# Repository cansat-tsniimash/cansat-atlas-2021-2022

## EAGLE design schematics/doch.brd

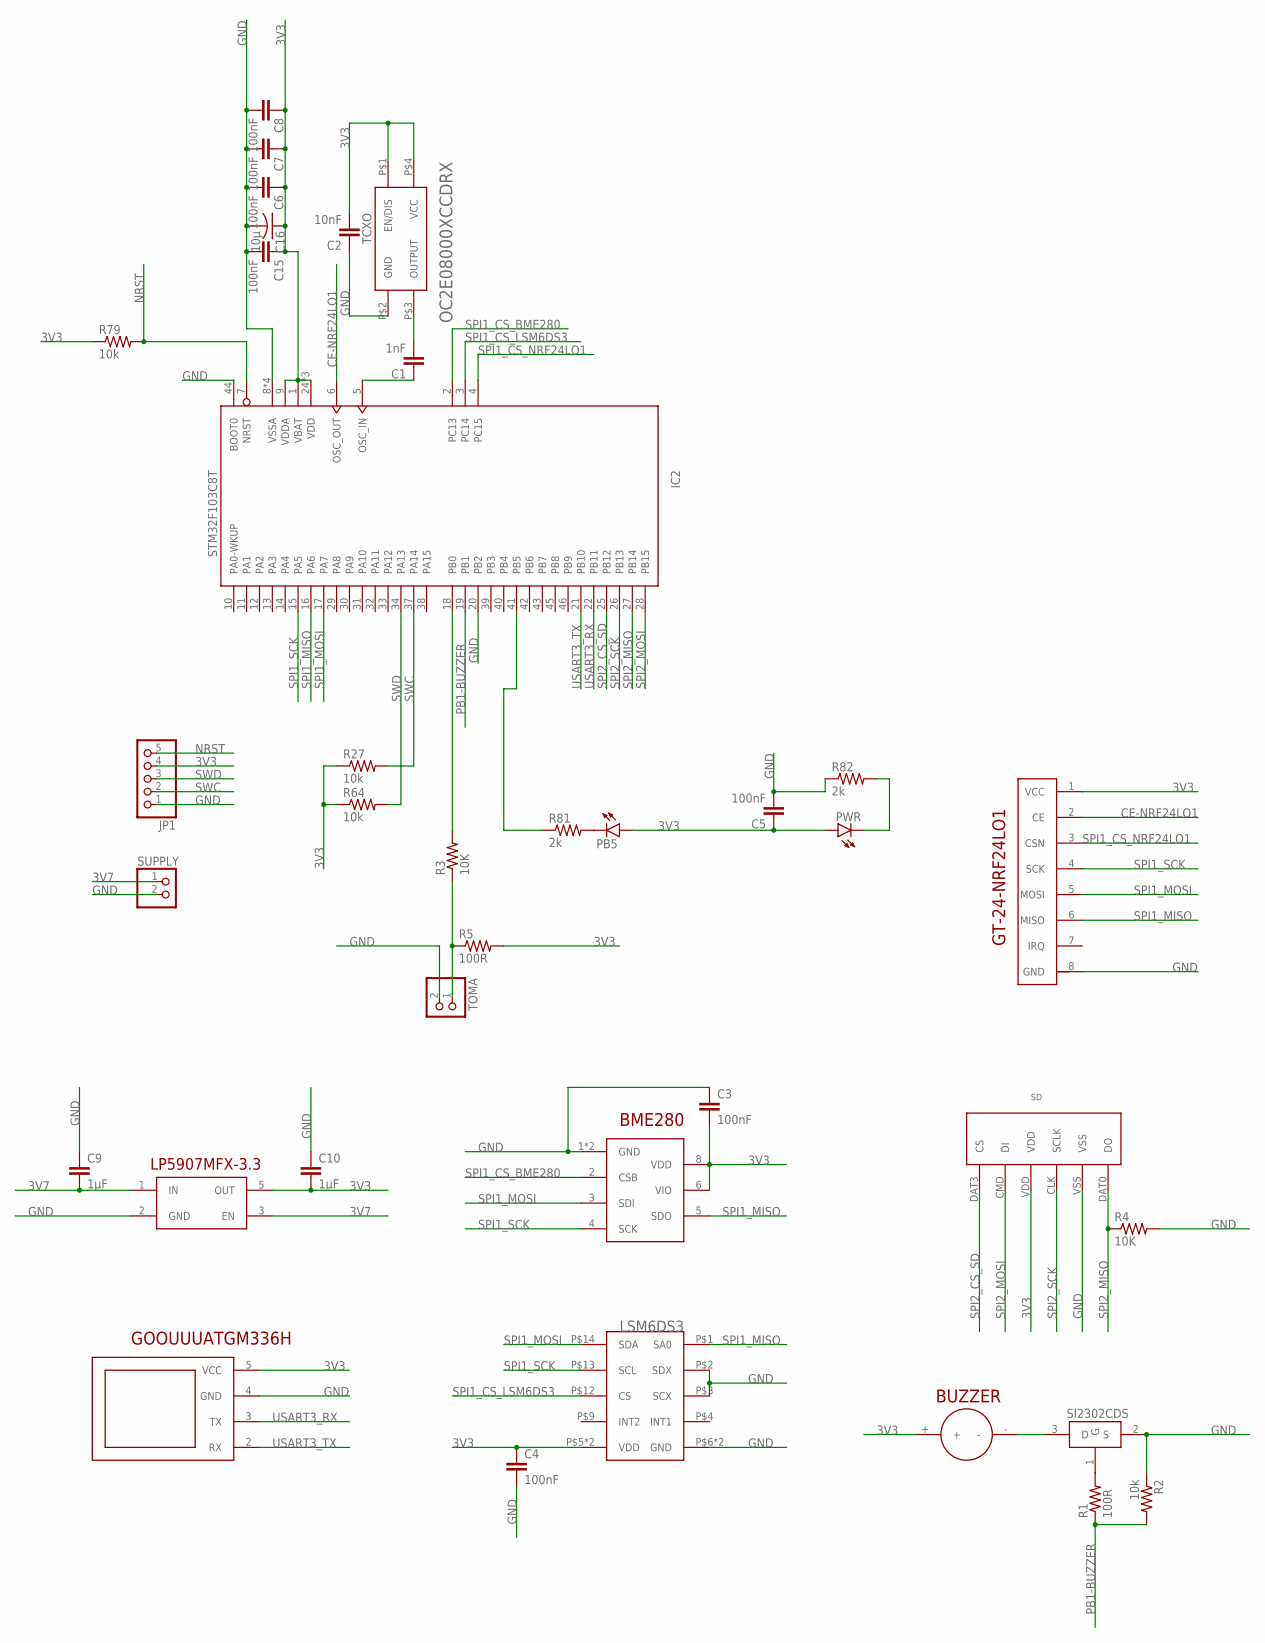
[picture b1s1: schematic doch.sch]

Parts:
BME280: BME280CHIP
BUZZER: BUZZER
C1: 1nF; C0603
C2: 10nF; C0603
C3, C4, C5, C6, C7, C8, C15: 100nF; C0603
C9, C10: 1μF; C0603
C16: 10µ; C1206
GOOUUUATGM336H: GOOUUUATGM336H
GT-24-NRF24LO1: GT-24-NRF24LO1
IC2: STM32F103C8T; LQFP48
JP1: PINHD-1X5; 1X05
LP5907MFX-3.3: LP5907MFX-3.3; 5PINSOT23
LSM6DS3: LSM6DS3; LGA-14
PB5: LEDCHIPLED_0603; CHIPLED_0603
PWR: LEDCHIPLED_0603; CHIPLED_0603
R1, R5: 100R; R0603
R2, R27, R64, R79: 10k; R0603
R3, R4: 10K; R0603
R81, R82: 2k; R0603
SD: SD-SPI; SD
SUPPLY: PINHD-1X2; 1X02
TCXO: OC2E08000XCCDRX
TOMA: PINHD-1X2/90; 1X02/90
U$1: SI2302CDS; SOT23-3

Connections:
3V3: BME280.6 (VIO), BME280.8 (VDD), BUZZER.+, C2.2, C3.2, C4.1, C5.1, C6.1, C7.1, C8.1, C10.2, C15.1, C16.1, GOOUUUATGM336H.5 (VCC), GT-24-NRF24LO1.1 (VCC), IC2.1 (VBAT), IC2.9 (VDDA), IC2.24 (VDD), IC2.36 (VDD), IC2.48 (VDD), JP1.4, LP5907MFX-3.3.5 (OUT), LSM6DS3.P$5 (VDD), LSM6DS3.P$8 (VDD), PB5.A, PWR.A, R5.2, R27.1, R64.1, R79.1, SD.VDD, TCXO.P$1 (EN/DIS), TCXO.P$4 (VCC)
3V7: C9.2, LP5907MFX-3.3.1 (IN), LP5907MFX-3.3.3 (EN), SUPPLY.1
CE-NRF24LO1: GT-24-NRF24LO1.2 (CE), IC2.6 (OSC_OUT)
GND: BME280.1 (GND), BME280.7 (GND), C2.1, C3.1, C4.2, C5.2, C6.2, C7.2, C8.2, C9.1, C10.1, C15.2, C16.2, GOOUUUATGM336H.4 (GND), GT-24-NRF24LO1.8 (GND), IC2.8 (VSSA), IC2.20 (PB2), IC2.23 (VSSA), IC2.35 (VSSA), IC2.44 (BOOT0), IC2.47 (VSSA), JP1.1, LP5907MFX-3.3.2 (GND), LSM6DS3.P$2 (SDX), LSM6DS3.P$3 (SCX), LSM6DS3.P$6 (GND), LSM6DS3.P$7 (GND), R2.1, R4.2, R82.1, SD.VSS, SUPPLY.2, TCXO.P$2 (GND), TOMA.2, U$1.2 (S)
unnamed: BUZZER.-, U$1.3 (D)
unnamed: R1.2, U$1.1 (G)
unnamed: C1.2, TCXO.P$3 (OUTPUT)
unnamed: C1.1, IC2.5 (OSC_IN)
unnamed: R3.1, R5.1, TOMA.1
unnamed: IC2.18 (PB0), R3.2
unnamed: PB5.C, R81.2
unnamed: PWR.C, R82.2
unnamed: IC2.41 (PB5), R81.1
NRST: IC2.7 (NRST), JP1.5, R79.2
PB1-BUZZER: IC2.19 (PB1), R1.1, R2.2
SPI1_CS_BME280: BME280.2 (CSB), IC2.2 (PC13)
SPI1_CS_LSM6DS3: IC2.3 (PC14), LSM6DS3.P$12 (CS)
SPI1_CS_NRF24LO1: GT-24-NRF24LO1.3 (CSN), IC2.4 (PC15)
SPI1_MISO: BME280.5 (SDO), GT-24-NRF24LO1.6 (MISO), IC2.16 (PA6), LSM6DS3.P$1 (SA0)
SPI1_MOSI: BME280.3 (SDI), GT-24-NRF24LO1.5 (MOSI), IC2.17 (PA7), LSM6DS3.P$14 (SDA)
SPI1_SCK: BME280.4 (SCK), GT-24-NRF24LO1.4 (SCK), IC2.15 (PA5), LSM6DS3.P$13 (SCL)
SPI2_CS_SD: IC2.25 (PB12), SD.DAT3 (CS)
SPI2_MISO: IC2.27 (PB14), R4.1, SD.DAT0 (DO)
SPI2_MOSI: IC2.28 (PB15), SD.CMD (DI)
SPI2_SCK: IC2.26 (PB13), SD.CLK (SCLK)
SWC: IC2.37 (PA14), JP1.2, R27.2
SWD: IC2.34 (PA13), JP1.3, R64.2
USART3_RX: GOOUUUATGM336H.3 (TX), IC2.22 (PB11)
USART3_TX: GOOUUUATGM336H.2 (RX), IC2.21 (PB10)

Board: 2 copper layers, 37 parts (7 on the bottom side), 29 nets, no tracks yet.

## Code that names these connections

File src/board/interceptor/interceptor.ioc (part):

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Mcu.Name=STM32F103C(8-B)Tx
Mcu.Package=LQFP48
Mcu.UserName=STM32F103C8Tx
PA10.GPIOParameters=GPIO_Speed,PinState,GPIO_ModeDefaultOutputPP
PA10.GPIO_ModeDefaultOutputPP=GPIO_MODE_OUTPUT_PP
PA10.GPIO_Speed=GPIO_SPEED_FREQ_HIGH
PA10.PinState=GPIO_PIN_SET
PA10.Signal=GPIO_Output
PA13.Mode=Serial_Wire
PA13.Signal=SYS_JTMS-SWDIO
PA14.Mode=Serial_Wire
PA14.Signal=SYS_JTCK-SWCLK
PA5.Mode=Full_Duplex_Master
PA5.Signal=SPI1_SCK
PA6.Mode=Full_Duplex_Master
PA6.Signal=SPI1_MISO
PA7.Mode=Full_Duplex_Master
PA7.Signal=SPI1_MOSI
PA8.GPIOParameters=GPIO_Speed,PinState,GPIO_Label
PA8.GPIO_Label=CE-NRF24L01
PA8.GPIO_Speed=GPIO_SPEED_FREQ_HIGH
PA8.PinState=GPIO_PIN_SET
PA8.Signal=GPIO_Output
PA9.Mode=Half_duplex(single_wire_mode)
PA9.Signal=USART1_TX
PB0.GPIOParameters=GPIO_Label
PB0.GPIO_Label=TOMA
PB0.Signal=GPIO_Input
PB1.GPIOParameters=GPIO_Speed,PinState,GPIO_Label
PB1.GPIO_Label=BUZZER
PB1.GPIO_Speed=GPIO_SPEED_FREQ_HIGH
PB1.PinState=GPIO_PIN_RESET
PB1.Signal=GPIO_Output
PB10.Mode=Asynchronous
PB10.Signal=USART3_TX
PB11.Mode=Asynchronous
PB11.Signal=USART3_RX
PB12.GPIOParameters=GPIO_Speed,PinState,GPIO_Label,GPIO_ModeDefaultOutputPP
PB12.GPIO_Label=CS-SD
PB12.GPIO_ModeDefaultOutputPP=GPIO_MODE_OUTPUT_PP
PB12.GPIO_Speed=GPIO_SPEED_FREQ_HIGH
PB12.PinState=GPIO_PIN_SET
PB12.Signal=GPIO_Output
PB13.Mode=Full_Duplex_Master
PB13.Signal=SPI2_SCK
PB14.Mode=Full_Duplex_Master
PB14.Signal=SPI2_MISO
PB15.Mode=Full_Duplex_Master
PB15.Signal=SPI2_MOSI
PB5.GPIOParameters=GPIO_Speed,GPIO_PuPd,GPIO_Label,GPIO_ModeDefaultOutputPP
PB5.GPIO_Label=LED
PB5.GPIO_ModeDefaultOutputPP=GPIO_MODE_OUTPUT_OD
PB5.GPIO_PuPd=GPIO_NOPULL
PB5.GPIO_Speed=GPIO_SPEED_FREQ_HIGH
PB5.Signal=GPIO_Output
PC13-TAMPER-RTC.GPIOParameters=GPIO_Speed,PinState,GPIO_Label
PC13-TAMPER-RTC.GPIO_Label=CS_BME280
PC13-TAMPER-RTC.GPIO_Speed=GPIO_SPEED_FREQ_HIGH
PC13-TAMPER-RTC.PinState=GPIO_PIN_SET
PC13-TAMPER-RTC.Signal=GPIO_Output
PC14-OSC32_IN.GPIOParameters=PinState,GPIO_Label
PC14-OSC32_IN.GPIO_Label=CS_LSM6DS3
PC14-OSC32_IN.PinState=GPIO_PIN_SET
PC14-OSC32_IN.Signal=GPIO_Output
PC15-OSC32_OUT.GPIOParameters=GPIO_Speed,PinState,GPIO_Label
PC15-OSC32_OUT.GPIO_Label=CS_NRF24L01
PC15-OSC32_OUT.GPIO_Speed=GPIO_SPEED_FREQ_HIGH
PC15-OSC32_OUT.PinState=GPIO_PIN_SET
PC15-OSC32_OUT.Signal=GPIO_Output
RCC.SYSCLKFreq_VALUE=64000000
RCC.SYSCLKSource=RCC_SYSCLKSOURCE_PLLCLK
board=custom

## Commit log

2021-12-15 Созданные Тимофеем модели NRF24l01 и ATGM366
2021-12-15 Добавила платы конструктора
2021-12-15 Начата разработка модели
2021-12-18 Добавил шпильку
2021-12-18 Удолил большие модельки стандартного конструктора
2021-12-18 поменял тяжелые модельки на лёгкие,добавил крышку и переходник
2021-12-22 Добавлен отсек для аккумулятора
2021-12-22 Добавил двигатель, отсек для ДА и переходники
2021-12-25 Разработан отсек для аккумулятора
2021-12-25 Добавила гайку М3
2021-12-26 Добавил отдельную папку для 3d печати
2021-12-26 Поменял размерность гайки
2021-12-26 Заменил служебный отсек МА
2021-12-26 Перенёс файлы в основную папку
2021-12-26 Добавил гайки основной модели
2021-12-29 Добавил stl версии для печати
2021-12-29 Изменения в модельках
2021-12-29 Убраны лишние файлы, изменен отсек аккумулятора и подложка датчика освещенности, начаты ДА
2021-12-30 Добавлены корректировки служебному отсеку
2022-01-04 Добавлен толкатель для отсека аккумулятора
2022-01-04 Добавлены stl для печати
2022-01-04 Перенесла все модели в папку со сборкой
2022-01-04 Добавлен TSL2561
2022-01-04 Внесены правки в отсек аккумулятра и в отсек двигателя, проведена работа над дочерними аппаратами
2022-01-06 Добавлен гаечный ключ М3
2022-01-06 stl для гаечного ключа и валика
2022-01-06 Добавлен цилиндр - имитатор пружинки
2022-01-06 Проведена работа над системой отделения ДА
2022-01-07 Поменял центральный вал и фиксатор
2022-01-07 Добавил стойки (14 и 11.5мм)
2022-01-07 Переделан отсек дочек, добавлен концевик
2022-01-07 Изменена основная сборка
2022-01-08 Удлинил штыри
2022-01-08 Изменён отсек дочек, добавлен концевик и место его крепления
2022-01-10 Добавлен отсек аккумулятора ДА и крепление ДА
2022-01-12 Добавил антену GPS
2022-01-12 добавил джампер
2022-01-16 Добавил пищалку
2022-01-16 Изменил служебный отсек, добавил в основную сборку
2022-01-20 Изменен Buzzer, tsl заменен на фотодиод
2022-01-20 Добавлен файл для печати корпуса ДА
2022-01-22 Изменена система отделения, облегчил служебный отсек
2022-01-22 Создан проект для работы с радио. Написаны функциичтения и записи в регистр и отправки команды
2022-01-26 Продолжаем работать над радио
2022-01-29 Печать: стойка 10мм и тестовый стэнд
2022-01-29 Добавил тестовый стэнд
2022-01-29 Убрал всё лишнее из файла (Спасибо, Вячеслав), добавил место крипления концевика (Спасибо, Вячеслав)
2022-01-29 Продолжаем работать над радил. Оно пока не работает.
2022-01-30 Добавил в сборку винты и гайки для концевика, изменил валик
2022-01-30 Добавил изменённый файл валика на печать, добавил список на печать
2022-01-30 Поправил валик
2022-01-30 Убраны лишние файлы
2022-01-30 Ловля багов в радио
2022-01-31 Поправил основную сборку
2022-01-31 Добавил новый вариант корпуса ДА, добавил разъём SD-карты и микроконтроллер ДА
2022-02-01 внес корректировки отсеку ДА, добавил пищалку и транзистор
2022-02-02 Дописали "нижние" функции
2022-02-02 Продолжаем сидеть с радио, оно снова не работает
2022-02-05 Начали писать код для МА
2022-02-10 Радио что-то отправляет
2022-02-10 Добавила общую библиотеку (ТЕСТ)
2022-02-12 Добавлена проверка на включение соответствующей переферии
2022-02-12 Пробунем добавить ссылку на библиотеку
2022-02-12 Драйвер радио перенесен в общую папку
2022-02-12 Радио работает
2022-02-12 Мейн изменен в соответствии с изменениями в драйвере
2022-02-16 Начал плату ДА
2022-02-19 Продолжение работы над платами
2022-02-19 3я часть Дочернего балета
2022-02-22 Актуальная библиотека
2022-02-23 Актуальная версия плат (и библиотеки)
2022-02-23 переписали main под верхний уровень
2022-02-23 Начал работу над физической платой, добавил радио
2022-02-26 Платы дочек: Новая надежда
2022-03-02 Дописали мейн для отправки сообщеня и успешно его отправили
2022-03-02 заставили программу принимать сообщение вместе с АСК
2022-03-05 актуализировали main
2022-03-16 настроили пины
2022-03-16 дописали отправку пакета на землю
2022-03-19 Поменяли название
2022-03-19 Создали проект для ДА
2022-03-19 Работа над переключателями МА
2022-03-19 начали писать радио ДА. настроили пины
2022-03-26 прикрутили UART, дописали код для запроса данных с ДА
2022-03-26 дописали код для отправки данных на МА , но 1-ый пакет идет чаще второго !
2022-03-29 прикрутили фоторезистор
2022-04-09 Добавили ГПС и алгоритм определения отделения по фоторезистору. ГПС не работает
2022-04-09 переписали гпс на прерывания
2022-04-09 Удолили папку дебаг
2022-04-09 добавили гпс
2022-04-09 Заставили ГПС работать
2022-04-09 Записываем данные ГПС напрямую в структуру с пакетом
2022-04-13 добавили датчик давления. ничего не робит 0(
2022-04-16 добавили бме + высота
2022-04-20 интегрировали радио
2022-04-23 Продолжаем работу над радио
2022-04-23 Библиотечка
2022-04-27 Добавили БМП, оно работет, добавили ЛСМ, оно не работает
2022-04-30 работает передача по радио бме и лсм. можно снимать видео
2022-04-30 Попытались добавить радио
2022-05-02 Изменения в пакетах, начинаем прикручивать фоторезистор
2022-05-03 Добавили фоторезистор
2022-05-03 Актуализировали датчики и радио
2022-05-04 добавили сд на МА (только первый пак)
2022-05-11 Сделали обмен с ДА
2022-05-12 Добились радиопередачи между ДА и МА
2022-05-25 добавили лис и дс18. переписали сд на бинарку
2022-06-01 Добавили crc
2022-06-01 Закинула парсер без проекта
2022-06-04 Добавили СД
2022-06-04 Балуемся с бортом
2022-06-04 Заставили работать разбор МА, добавили ДА
2022-06-08 начали пареписывать радио
2022-06-08 Попытки завести сд
2022-06-09 Исправлен омерзительный баг в драйвере SD карты
2022-06-10 Переписали радио
2022-06-10 Дописали состояния, не тестили
2022-06-10 Дописали заполнение пакета. Надо тестить
2022-06-10 Заработало, но вяло. Необходимы дальнейшие тесты
2022-06-11 нмичего не работает
2022-06-11 Убрала метадату
2022-06-11 Парсер
2022-06-11 Исправил ошибки в парсере
2022-06-11 опять ничего не робит
2022-06-12 Заводим радио
2022-06-14 сд робит. Поменяли настройки сд.
2022-06-15 сд робит. высоту считаем.
2022-06-16 изменения по высоте от бме
2022-06-16 попереставляли. исправили фикс. убрали лишнее.
2022-06-17 Вот эта дич робит.
2022-06-18 Заводим радио в мастере
2022-06-18 Выставлен нужный спай
2022-06-18 сделали радио
2022-06-21 Добавили 3 Да и лампочку
2022-06-21 минус лишняя лампочка
2022-06-21 добавили разделение ДА, лампочка пореже
2022-06-21 добавили пищалку.
2022-06-21 файлик с ДА
2022-06-21 с ДА принимает. на землю не шлет
2022-06-23 Новый мавлинк
2022-06-24 пищалка работает
2022-06-24 поправили пакет
2022-06-24 Поправила тригер двигателя и сопротивление резистора
2022-06-24 Радио передает, но медленно
2022-06-25 ускоряем радио
2022-06-28 Заводим радио + сд
2022-06-28 Делаем парсер
2022-06-28 Радио робит
2022-06-28 Убрала лишнее
2022-06-29 Безопасное СД
2022-06-29 тестим
2022-06-30 SD + IWDG
2022-07-01 огоньки
2022-07-01 поправочный коммит. все вроде собирается
2022-07-01 Библиотека снова уплыла
2022-07-01 Лампочка на фикс, более редкая СД и таймаут на радио
2022-07-01 Апдейт СД + вотчдог
2022-07-01 либа
2022-07-05 Все, что добыли по данным. Есть и мусор
2022-07-05 Финальный билд
